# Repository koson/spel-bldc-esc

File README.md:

# SPEL electronic speed controller for BLDC motors 

Open-source hardware and software for BLDC motor electronic speed controller.

### About
Yet another open-source BLDC motor controller, developed primarily as a learning project. 

The end-goal is to create a controller that would be compact, flexibla and cheap to manufacture (design rules compliant with the ones from JLCPCB - 
same goes for most of the electronic components available at their SMD/SMT parts library). 

### Specification:
- Rated voltage: 60 [VDC]
- Rated current: 60 [ADC]
- Communication interfaces: CAN, I2C, UART, USB
- Debugging interface: SWD
- Control methods: through comm. interfaces, STEP/DIRECTION
- Feedback: Encoder inputs (reprogrammable to HAL sensor inputs), current sensing, back-EMF measurement. 
- CPU: STM32F103C8Tx/STM32F103CBTx series 
- Motor driver: Texas Instrument's DRV8301 
- Protection: DRV8301's built-in overcurrent/overvoltage protection modules, braking resistor.

### Hardware renders 

*SWD - IRL would be a pin header, not a socket, 3D model used for a footprint that happened to fit pin numeration accurately

### TODO: 
- BOM
- Manufacturing outlines (listing cheapest options, and possible part substitutes)
- Append calculations (somewhere)

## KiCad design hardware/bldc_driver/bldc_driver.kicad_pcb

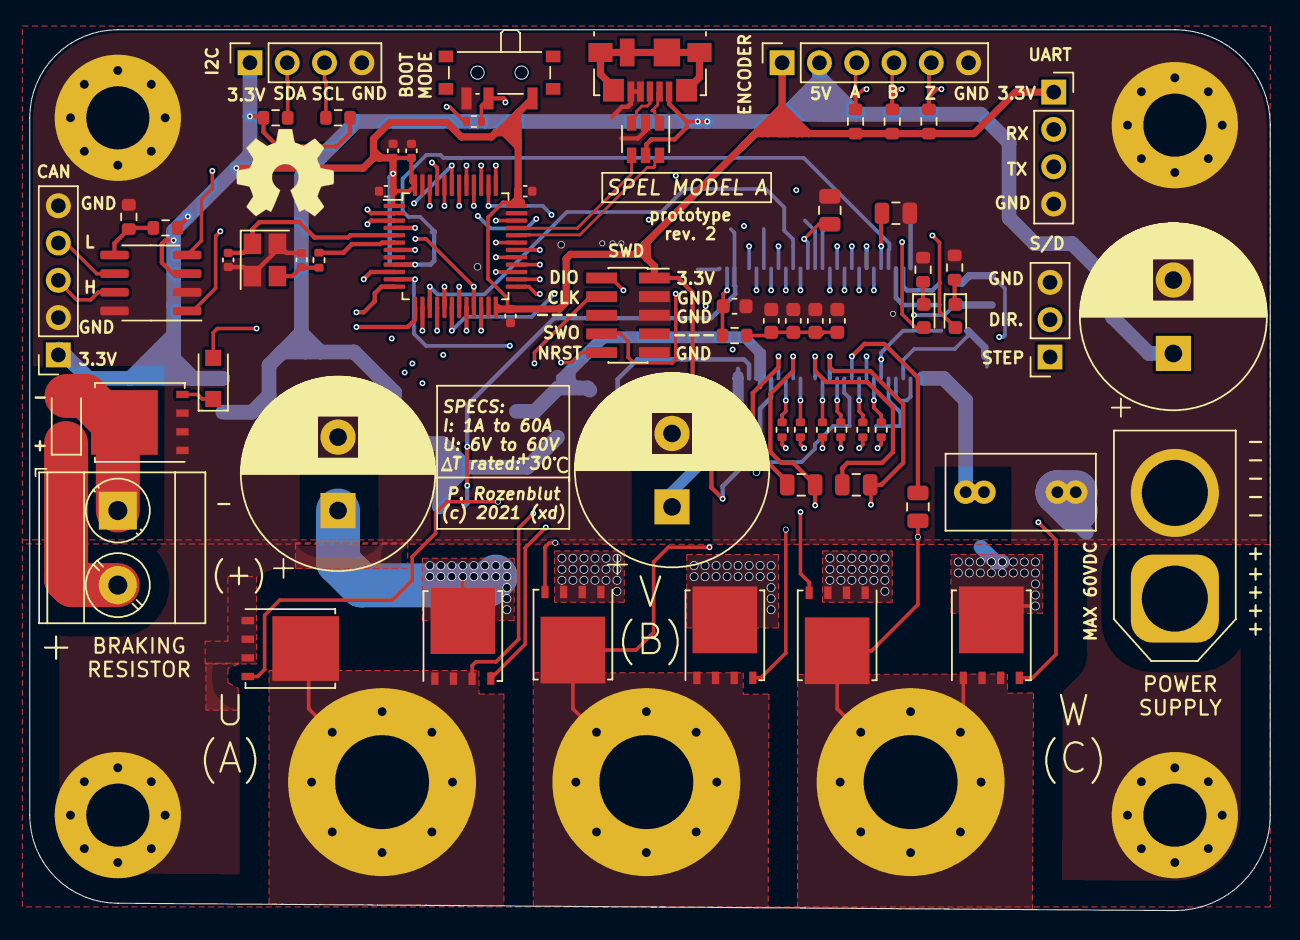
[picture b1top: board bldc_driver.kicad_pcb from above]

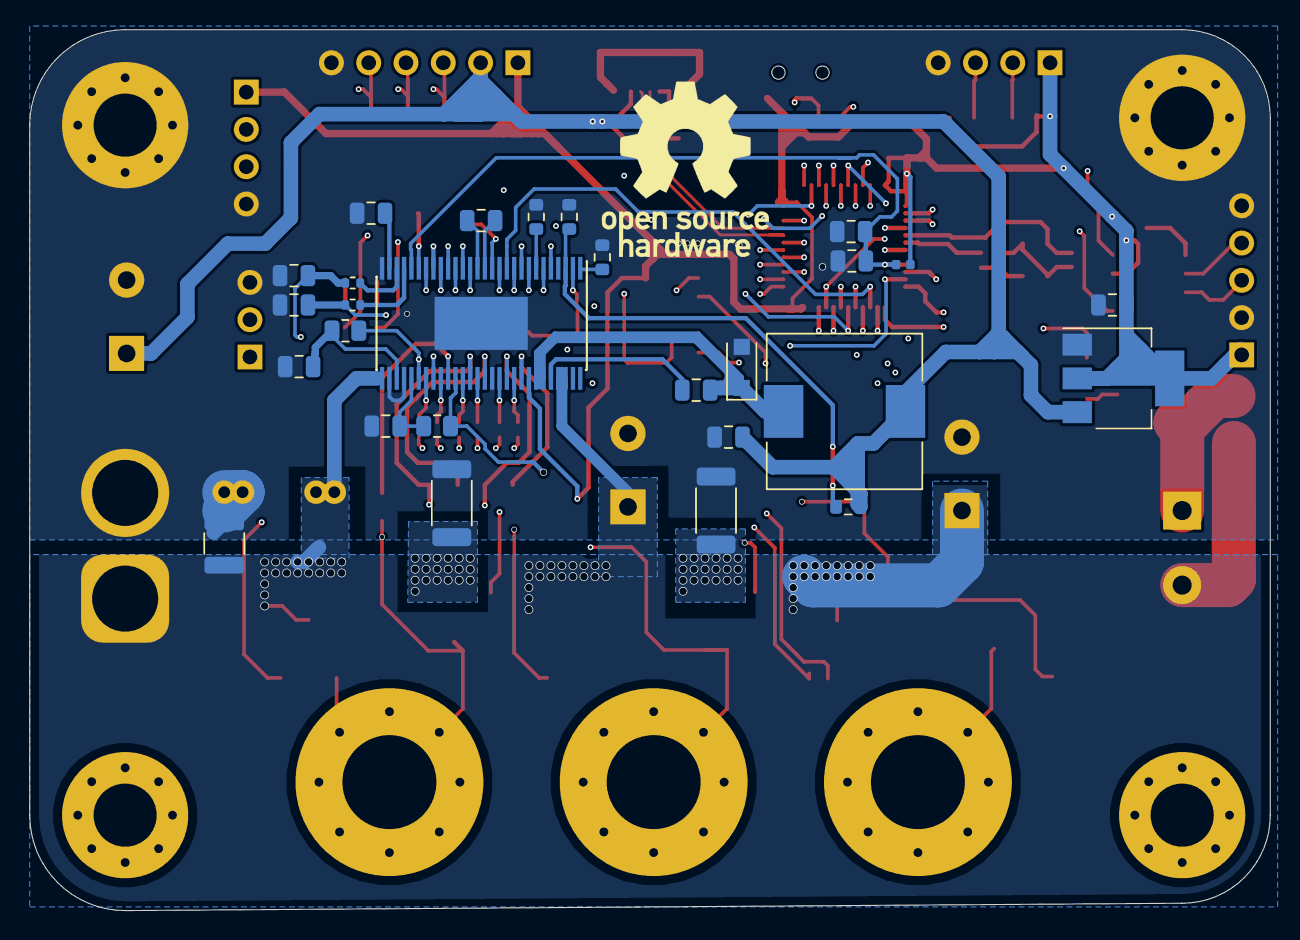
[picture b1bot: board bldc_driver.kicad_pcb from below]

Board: 4 copper layers, 84.5 x 60.0 mm, 98 parts (27 on the bottom side), 91 nets.

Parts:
C1, C3, C5, C33: 100n; C_0402_1005Metric
C2, C4: 12p; C_0402_1005Metric
C6: 4.7u; C_0402_1005Metric
C7: 1u; C_0805_2012Metric
C8: 10n; C_0805_2012Metric
C9, C16, C19, C20: 2.2u; C_0805_2012Metric
C10: 4.7u; C_0805_2012Metric
C11, C12, C21, C28: 2.2n; C_0805_2012Metric
C13, C23, C24, C25: 100n; C_0805_2012Metric
C14: 68u; CP_Radial_D12.5mm_P5.00mm
C15, C17: 680uF_63V; CP_Radial_D13.0mm_P5.00mm
C18: 22n; C_0805_2012Metric
C22, C26, C27, C31: 82p; C_0603_1608Metric
C29: 68n; C_Rect_L10.0mm_W5.0mm_P5.00mm_P7.50mm
C30: 4.7u; C_1210_3225Metric
C32: 22p; C_0603_1608Metric
D1: LED_BLUE; LED_0603_1608Metric
D2: LED_GREEN; LED_0603_1608Metric
D3: dname; D_SOD-123F
D4: d; D_SOD-123F
D5: Flyback; D_SOD-123F
H1, H2, H3, H4: MountingHole_Pad; MountingHole_4.3mm_M4_Pad_Via
J1: Conn_01x03; PinSocket_1x03_P2.54mm_Vertical
J2, J5: Conn_01x04; PinSocket_1x04_P2.54mm_Vertical
J3: Conn_01x05; PinSocket_1x05_P2.54mm_Vertical
J4: Conn_01x06; PinSocket_1x06_P2.54mm_Vertical
J6: USB_B_Micro; USB_Micro-B_Molex_47346-0001
J7: SWD; PinSocket_2x05_P1.27mm_Vertical_SMD
J8: Power_Supply; AMASS_XT60-F_1x02_P7.20mm_Vertical
J9: Braking_resistor_terminal; TerminalBlock_Phoenix_MKDS-3-2-5.08_1x02_P5.08mm_Horizontal
J10: U; motor_driving_pad_hole
J11: V; motor_driving_pad_hole
J12: W; motor_driving_pad_hole
L1: 39n; L_0402_1005Metric
L2: 22u; L_10.4x10.4_H4.8
Q1, Q2, Q3, Q4, Q5, Q6, Q7: BSC110N
R1: 10k; R_0402_1005Metric
R2, R15, R16: 47; R_0402_1005Metric
R3, R4, R26, R27, R28: 2.2k; R_0603_1608Metric
R5, R6: 1.5k; R_0603_1608Metric
R7, R8: 1k; R_0603_1608Metric
R9, R10: 120; R_0805_2012Metric
R11, R13: 18k; R_0603_1608Metric
R12: 3.3k; R_0603_1608Metric
R14: 220k; R_0603_1608Metric
R17: 47k; R_0603_1608Metric
R18, R19, R20, R21, R23, R24: 10; R_0402_1005Metric
R22, R25: 10m; R_2010_5025Metric
SW1: SW_SPDT; SW_SPDT_PCM12
U1: AMS1117-3.3; SOT-223-3_TabPin2
U2: STM32F103CBTx; LQFP-48_7x7mm_P0.5mm
U3: USBLC6-2SC6; SOT-23-6
U4: SN65HVD230; SOIC-8_3.9x4.9mm_P1.27mm
U6: DRV8301DCAR; HTSSOP-56-1EP_6.1x14mm_P0.5mm_EP3.61x6.35mm
Y1: Crystal_GND24; Crystal_SMD_3225-4Pin_3.2x2.5mm

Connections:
+3.3VA: C7.1, C8.1, L1.2, U2.9, U6.24
+3V3: C1.1, C3.1, C5.1, C6.1, C10.1, C33.1, J2.1, J3.1, J4.1, J5.1, J7.1, L1.1, R3.1, R4.1, R7.1, R26.1, R27.1, R28.1, SW1.1, U1.2, U2.1, U2.24, U2.36, U2.48, U4.3, U6.49
+5V: C9.1, C14.1, J4.2, J6.1, L2.2, R11.1, U1.3, U3.5
+VDC: C15.1, C17.1, C29.1, C30.1, D5.1, J8.1, J9.2, Q1.3, Q3.3, Q6.3, U6.29, U6.53, U6.54
-VDC: C1.2, C2.2, C3.2, C4.2, C5.2, C6.2, C7.2, C8.2, C9.2, C10.2, C11.1, C12.1, C14.2, C15.2, C16.2, C17.2, C19.1, C20.2, C21.2, C22.1, C26.1, C27.1, C28.2, C29.2, C30.2, C31.1, C32.2, C33.2, D3.2, H1.1, H2.1, H3.1, H4.1, J1.3, J2.4, J3.2, J3.5, J4.6, J5.4, J6.4, J6.5, J7.3, J7.5, J7.9, J8.2, Q2.1, Q5.1, R5.2, R6.2, R8.2, R12.2, R13.1, R14.2, R22.2, R25.2, SW1.3, U1.1, U2.8, U2.23, U2.35, U2.47, U3.2, U4.2, U4.8, U6.28, U6.30, U6.32, U6.44, U6.57, Y1.2, Y1.4
/control_elements/AVDD: C16.1, U6.27
/control_elements/BST_BK: C13.1, U6.52
/control_elements/GH_A: R18.2, U6.47
/control_elements/GH_B: R20.2, U6.42
/control_elements/GH_C: R23.2, U6.37
/control_elements/GL_A: R19.2, U6.45
/control_elements/GL_B: R21.2, U6.40
/control_elements/GL_C: R24.2, U6.35
/control_elements/GVDD: C19.2, U6.13
/control_elements/PH_0: C13.2, D3.1, L2.1, U6.50, U6.51
/control_elements/SH_A: C23.1, J10.1, Q1.1, Q2.3, U6.46
/control_elements/SH_B: C24.2, J11.1, Q3.1, Q4.3, U6.41
/control_elements/SH_C: C25.1, J12.1, Q6.1, Q7.3, U6.36
/control_elements/SL_B: Q4.1, R9.1, R22.1, U6.39
/control_elements/SL_C: Q7.1, R10.2, R25.1, U6.34
BOOT0: R1.1, U2.44
BRAKING_PWM: D4.2, U2.43
CAN_H: J3.3, U4.7
CAN_L: J3.4, U4.6
CAN_RX: U2.45, U4.4
CAN_TX: U2.46, U4.1
CONTROL_DIRECTION: J1.2, U2.3
CONTROL_STEP: J1.1, U2.2
DC_CAL: U2.18, U6.12
DRV_A_HIGH: U2.29, U6.17
DRV_A_LOW: U2.26, U6.18
DRV_B_HIGH: U2.30, U6.19
DRV_B_LOW: U2.27, U6.20
DRV_C_HIGH: U2.31, U6.21
DRV_C_LOW: U2.28, U6.22
ENCODER_A: J4.3, R26.2, U2.40
ENCODER_B: J4.4, R27.2, U2.41
ENCODER_Z: J4.5, R28.2, U2.42
EN_GATE: U2.25, U6.16
HS_OSC_IN: C2.1, U2.5, Y1.1
HS_OSC_OUT: R2.2, U2.6
I2C_SCL: J5.3, R4.2, U2.21
I2C_SDA: J5.2, R3.2, U2.22
LED_FLAG_1: D1.2, U2.38
LED_FLAG_2: D2.2, U2.4
NRST: J7.10, U2.7
unnamed: C4.1, R2.1, Y1.3
unnamed: C11.2, R9.2, U6.33
unnamed: C12.2, R10.1, U6.31
unnamed: C18.1, U6.15
unnamed: C18.2, U6.14
unnamed: C20.1, U6.23
unnamed: C22.2, C27.2, C31.2, C32.1, R17.1
unnamed: C23.2, U6.48
unnamed: C24.1, U6.43
unnamed: C25.2, U6.38
unnamed: C26.2, R17.2, U6.2
unnamed: D1.1, R5.1
unnamed: D2.1, R6.1
unnamed: D4.1, Q5.2
unnamed: D5.2, J9.1, Q5.3
unnamed: Q1.2, R18.1
unnamed: Q2.2, R19.1
unnamed: Q3.2, R20.1
unnamed: Q4.2, R21.1
unnamed: Q6.2, R23.1
unnamed: Q7.2, R24.1
unnamed: R1.2, SW1.2
unnamed: R7.2, R8.1, U4.5
unnamed: R11.2, R12.1, U6.3
unnamed: R13.2, U6.7
unnamed: R14.1, U6.1
unnamed: R15.1, U6.25
unnamed: R16.2, U6.26
SO1: C28.1, R15.2, U2.10
SO2: C21.1, R16.1, U2.11
SPI_MISO_CPU_SIDE: U2.16, U6.10
SPI_MOSI_CPU_SIDE: U2.17, U6.9
SPI_NSS: U2.14, U6.8
SPI_SCK: U2.15, U6.11
SYS_JTCK_SWCLK: J7.4, U2.37
SYS_JTDO_TRACESWO: J7.8, U2.39
SYS_JTMS_SWDIO: J7.2, U2.34
USART_RX: J2.2, U2.13
USART_TX: J2.3, U2.12
USB_CONN_D+: J6.3, U3.3
USB_CONN_D-: J6.2, U3.1
USB_D+: U2.33, U3.4
USB_D-: U2.32, U3.6
nFAULT: U2.20, U6.6
nOCTW: U2.19, U6.5

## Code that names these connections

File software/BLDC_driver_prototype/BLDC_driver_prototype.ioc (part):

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Mcu.Name=STM32F103C(8-B)Tx
Mcu.Package=LQFP48
Mcu.UserName=STM32F103CBTx
PA0-WKUP.GPIOParameters=GPIO_Label
PA0-WKUP.GPIO_Label=SO1
PA0-WKUP.Signal=ADCx_IN0
PA1.GPIOParameters=GPIO_Label
PA1.GPIO_Label=SO2
PA1.Signal=ADCx_IN1
PA10.Signal=S_TIM1_CH3
PA11.Mode=Device
PA11.Signal=USB_DM
PA12.Mode=Device
PA12.Signal=USB_DP
PA13.Mode=Trace_Asynchronous_SW
PA13.Signal=SYS_JTMS-SWDIO
PA14.Mode=Trace_Asynchronous_SW
PA14.Signal=SYS_JTCK-SWCLK
PA15.GPIOParameters=GPIO_Label
PA15.GPIO_Label=LED_FLAG_1
PA15.Signal=GPIO_Output
PA2.Mode=Asynchronous
PA2.Signal=USART2_TX
PA3.Mode=Asynchronous
PA3.Signal=USART2_RX
PA4.Mode=NSS_Signal_Hard_Output
PA4.Signal=SPI1_NSS
PA5.Mode=Full_Duplex_Master
PA5.Signal=SPI1_SCK
PA6.Mode=Full_Duplex_Master
PA6.Signal=SPI1_MISO
PA7.Mode=Full_Duplex_Master
PA7.Signal=SPI1_MOSI
PA8.Signal=S_TIM1_CH1
PA9.Signal=S_TIM1_CH2
PB0.GPIOParameters=GPIO_Label
PB0.GPIO_Label=DC_CAL
PB0.Signal=GPIO_Output
PB1.GPIOParameters=GPIO_Label
PB1.GPIO_Label=nOCTW
PB1.Signal=GPXTI1
PB10.Mode=I2C
PB10.Signal=I2C2_SCL
PB11.Mode=I2C
PB11.Signal=I2C2_SDA
PB12.GPIOParameters=GPIO_Label
PB12.GPIO_Label=EN_GATE
PB12.Signal=GPIO_Output
PB13.Mode=PWM Generation1 CH1 CH1N
PB13.Signal=TIM1_CH1N
PB14.Mode=PWM Generation2 CH2 CH2N
PB14.Signal=TIM1_CH2N
PB15.Mode=Output Compare3 CH3 CH3N
PB15.Signal=TIM1_CH3N
PB2.GPIOParameters=GPIO_Label
PB2.GPIO_Label=nFAULT
PB2.Signal=GPXTI2
PB3.Mode=Trace_Asynchronous_SW
PB3.Signal=SYS_JTDO-TRACESWO
PB4.GPIOParameters=GPIO_Label
PB4.GPIO_Label=ENCODER_A
PB4.Signal=GPXTI4
PB5.GPIOParameters=GPIO_Label
PB5.GPIO_Label=ENCODER_B
PB5.Signal=GPXTI5
PB6.GPIOParameters=GPIO_Label
PB6.GPIO_Label=ENCODER_Z
PB6.Signal=GPXTI6
PB7.GPIOParameters=GPIO_Label
PB7.GPIO_Label=BRAKING_PWM
PB7.Signal=S_TIM4_CH2
PB8.Mode=CAN_Activate
PB8.Signal=CAN_RX
PB9.Mode=CAN_Activate
PB9.Signal=CAN_TX
PC13-TAMPER-RTC.GPIOParameters=GPIO_Label
PC13-TAMPER-RTC.GPIO_Label=CONTROL_STEP
PC13-TAMPER-RTC.Signal=GPXTI13
PC14-OSC32_IN.GPIOParameters=GPIO_Label
PC14-OSC32_IN.GPIO_Label=CONTROL_DIRECTION
PC14-OSC32_IN.Signal=GPIO_Input
PC15-OSC32_OUT.GPIOParameters=GPIO_Label
PC15-OSC32_OUT.GPIO_Label=LED_FLAG_2
PC15-OSC32_OUT.Signal=GPIO_Output
PD0-OSC_IN.Mode=HSE-External-Oscillator
PD0-OSC_IN.Signal=RCC_OSC_IN
PD1-OSC_OUT.Mode=HSE-External-Oscillator
PD1-OSC_OUT.Signal=RCC_OSC_OUT
board=custom

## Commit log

2021-10-23 init
    - Pushed all the project files from the second project revision
2021-10-23 init software files
    - added STM32 configuration file
2021-10-23 Create README.md
    - forgot about the braking resistor
2021-10-23 added OSHW logos
2021-10-28 Cosmetic - trace improvements
    - correcting 3-way trace intersections
2021-10-28 Cosmetics
    -> Trace corrections cont'd

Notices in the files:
hardware/bldc_driver/bldc_driver.kicad_pcb:
(c) 2021 (xd)
